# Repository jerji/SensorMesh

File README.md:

# SensorMesh
Wireless mesh sensor network based on the ESP8266 and DHT22

This is a project I did for a client with a farm.
He needed a multitude of sensors to monitor the temperature in his beehives, freezers and buildings.
It is made with the arduino IDE and various repositories

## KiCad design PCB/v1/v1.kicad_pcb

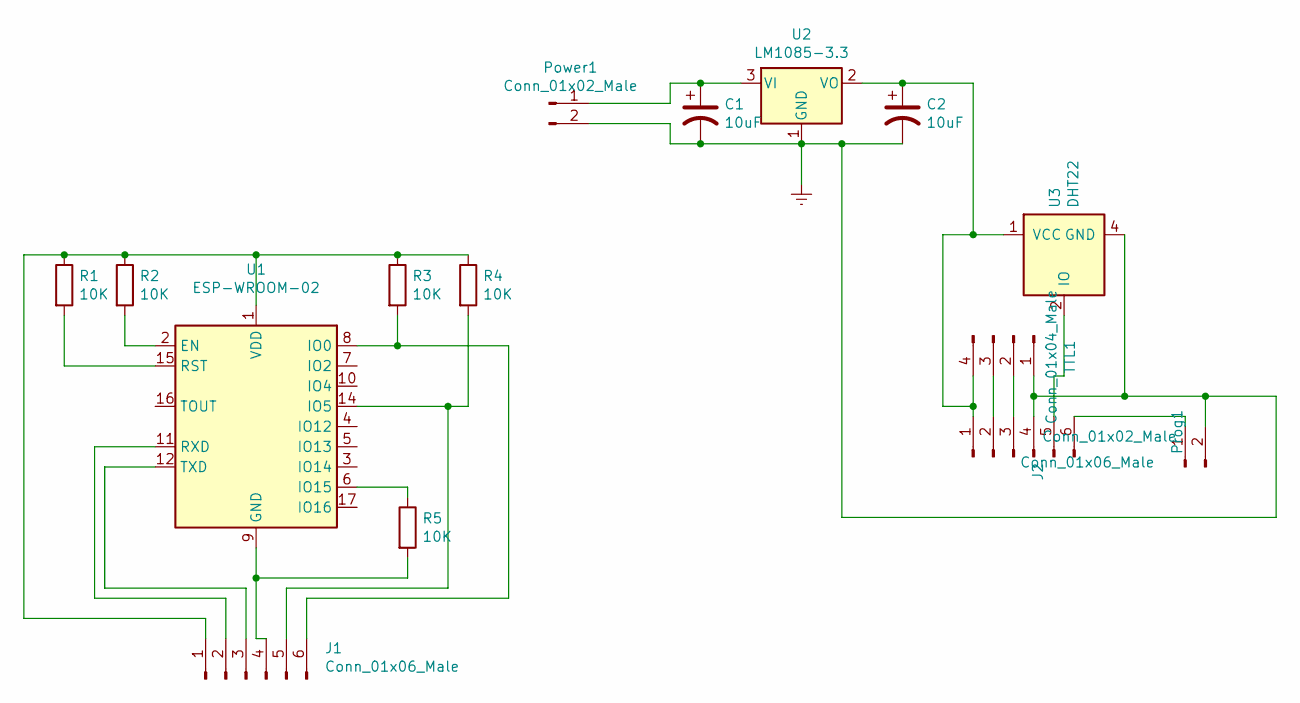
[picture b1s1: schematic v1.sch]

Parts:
C1, C2: 10uF; CP_Radial_Tantal_D4.5mm_P2.50mm
J1, J2: Conn_01x06_Male; PinHeader_1x06_P2.54mm_Vertical
Power1: Conn_01x02_Male; PinHeader_1x02_P2.54mm_Vertical
Prog1: Conn_01x02_Male; PinHeader_1x02_P2.54mm_Vertical
R1, R2, R3, R4, R5: 10K; R_1206_3216Metric_Pad1.42x1.75mm_HandSolder
TTL1: Conn_01x04_Male; PinHeader_1x04_P2.54mm_Vertical
U1: ESP-WROOM-02
U2: LM1085-3.3; TO-220-3_Vertical
U3: DHT22; DHT22_Temperature_Humidity

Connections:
Earth: C1.2, C2.2, J2.4, Power1.2, Prog1.2, TTL1.1, U2.1 (GND), U3.4 (GND)
unnamed: C1.1, Power1.1, U2.3 (VI)
unnamed: C2.1, J2.1, TTL1.4, U2.2 (VO), U3.1 (VCC)
unnamed: J1.1, R1.1, R2.1, R3.1, R4.1, U1.1 (VDD)
unnamed: J1.2, U1.11 (RXD)
unnamed: J1.3, U1.12 (TXD)
unnamed: J1.4, R5.2, U1.9 (GND), U1.13 (GND), U1.18 (GND), U1.19 (GND)
unnamed: J1.5, R4.2, U1.14 (IO5)
unnamed: J1.6, R3.2, U1.8 (IO0)
unnamed: J2.2, TTL1.3
unnamed: J2.3, TTL1.2
unnamed: J2.5, U3.2 (IO)
unnamed: J2.6, Prog1.1
unnamed: R1.2, U1.15 (RST)
unnamed: R2.2, U1.2 (EN)
unnamed: R5.1, U1.6 (IO15)

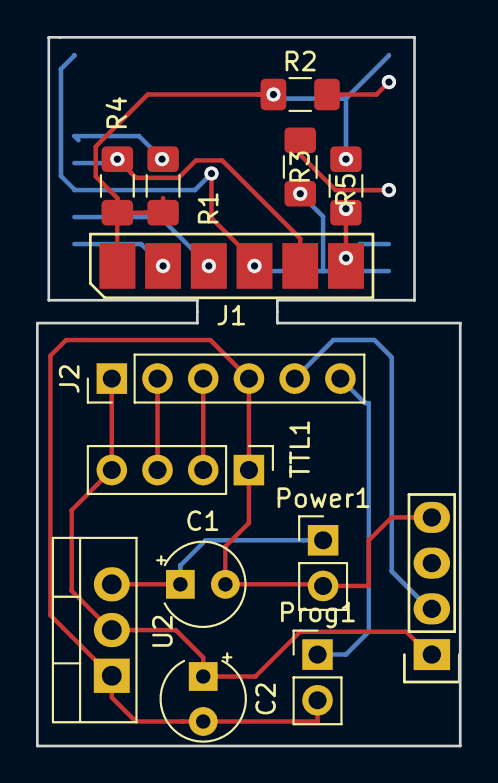
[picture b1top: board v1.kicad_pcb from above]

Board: 2 copper layers, 23.5 x 39.4 mm, 15 parts (1 on the bottom side), 16 nets.
